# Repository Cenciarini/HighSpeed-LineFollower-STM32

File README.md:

# 🚀 High-Speed Line Follower Robot — STM32 Bluepill

---

## 📖 Descripción general

Este proyecto presenta el desarrollo completo de un **robot móvil seguidor de línea de alta velocidad**, basado en un **microcontrolador STM32F103C8T6 (Bluepill)**.  
El sistema fue diseñado para lograr **gran precisión y estabilidad a altas velocidades** mediante el uso de **controladores PID independientes para cada rueda** y una arquitectura modular que integra hardware, firmware, modelado 3D y una interfaz de control desde PC.

El robot combina múltiples disciplinas de ingeniería:  
- ⚙️ **Diseño electrónico y PCB**  
- 💻 **Programación embebida en C**  
- 🧠 **Control en tiempo real (PID)**  
- 🌐 **Comunicación inalámbrica vía ESP32 / UDP**  
- 🖥️ **Interfaz gráfica en C++ con Qt Creator**  
- 🧩 **Diseño mecánico en SolidWorks**

---

## 🧰 Estructura del repositorio

```
📦 RobotLineFollower_STM32
│
├── PCB_Micro/
│   ├── schematics/
│   ├── gerbers/
│   └── README.md
│   📘 Contiene el diseño electrónico completo en KiCAD.
│
├── QT_Micro/
│   ├── mainwindow.cpp
│   ├── resources/
│   └── README.md
│   💻 Interfaz de usuario en Qt Creator (C++) para control remoto y monitoreo.
│
├── SOLID_Micro/
│   ├── ensamblajes/
│   ├── piezas/
│   └── archivos_stl/
│   🧩 Modelos 3D y partes imprimibles diseñadas en SolidWorks.
│
├── ST_Micro/
│   ├── Core/
│   ├── Drivers/
│   ├── Src/
│   └── Inc/
│   ⚙️ Proyecto en STM32CubeIDE con firmware completo para el Bluepill.
│
└── README.md
```

---

## ⚙️ ST_Micro — Firmware embebido

El firmware principal está implementado en **C** dentro de `STM32CubeIDE`, con soporte para múltiples periféricos del microcontrolador.  
Entre sus módulos más relevantes se incluyen:

### 🔧 Periféricos utilizados
- **I2C:** Lectura de sensor **MPU6050** (acelerómetro + giroscopio).  
- **DMA:** Adquisición continua de señales **ADC** para los sensores IR.  
- **PWM:** Control preciso de la velocidad de cada motor DC.  
- **UART:** Comunicación con módulo **ESP01 (WiFi)** para envío de datos vía UDP.  
- **Timers:** Sincronización de tareas y control de tiempo de muestreo.  
- **ADC:** Lectura analógica de los sensores de línea.  

### 🧠 Control PID
El control PID ajusta dinámicamente las velocidades de ambas ruedas para mantener el robot centrado sobre la línea incluso en curvas pronunciadas o a altas velocidades.

El algoritmo se ejecuta en tiempo real y los parámetros **Kp, Ki, Kd** pueden modificarse desde la interfaz gráfica mediante comunicación **UDP**.

### 🧾 Librerías implementadas
- `comunicaciones.c`: Implementa un protocolo propio con chequeo de errores y estructura de tramas (`HEADER`, `NBYTES`, `PAYLOAD`, `CKS`).  
- `ESP01.c`: Gestión completa del módulo WiFi ESP01 con comandos AT y control de estados.  
- `ssd1306.c` y `fonts.c`: Control del display OLED (visualización de estados del robot).  
- `main.c`: Orquesta la lógica principal, incluyendo adquisición de datos, control PID, comunicación, y visualización en pantalla.

---

## 💻 QT_Micro — Interfaz gráfica de control

Desarrollada en **Qt Creator (C++)**, esta interfaz permite:

- Conexión con el robot a través de **UDP (ESP32 o ESP01)**.  
- Ajuste dinámico de parámetros PID (Kp, Ki, Kd) para cada rueda.  
- Visualización en tiempo real de:
  - Estado del robot y sensores IR.
  - Gráficos del recorrido.
  - Datos del MPU6050 (ángulos, aceleraciones).  
- Control remoto del robot (inicio/parada, velocidad base, direcciones, etc.).

---

## ⚡ PCB_Micro — Electrónica y PCB

Diseñada completamente en **KiCAD**, esta placa integra:

- Microcontrolador **STM32F103C8T6** (Bluepill).  
- Etapa de potencia con control PWM para motores DC.  
- Sensores IR analógicos para detección de línea.  
- Reguladores de tensión y protección de alimentación.  
- Conectores para display OLED, ESP01, MPU6050 y ST-Link.  

Incluye:
- Archivos **.sch** (esquemáticos)
- Archivos **.kicad_pcb**
- Archivos **Gerber** listos para fabricación

---

## 🧩 SOLID_Micro — Diseño mecánico

El diseño mecánico del robot fue modelado íntegramente en **SolidWorks**, con foco en minimizar peso y tamaño manteniendo la rigidez estructural.  
Se incluyen:
- Ensambles del chasis y soporte de sensores.  
- Piezas STL listas para impresión 3D.  
- Montaje optimizado del PCB y baterías.

---

## 📡 Comunicación y protocolo

El robot y la interfaz de PC se comunican mediante **UDP**, usando un **protocolo propio de mensajes binarios** desarrollado en C.  
Cada mensaje posee estructura de seguridad y verificación de checksum, garantizando robustez en entornos de alta velocidad.

---

## 🧠 Principales características técnicas

| Componente | Descripción |
|-------------|-------------|
| **Microcontrolador** | STM32F103C8T6 (Cortex-M3, 72 MHz) |
| **Sensores** | IR analógicos + MPU6050 (I2C) |
| **Pantalla** | OLED SSD1306 (I2C) |
| **Comunicación** | ESP01 (UART → UDP) / Interfaz Qt |
| **Control** | PID doble canal (rueda izquierda / derecha) |
| **Alimentación** | Batería Li-Po 7.4V con regulación interna |
| **Software principal** | STM32CubeIDE, KiCAD, Qt Creator, SolidWorks |

---

## 🧠 Habilidades demostradas

Este proyecto refleja competencias avanzadas en:

- Diseño y fabricación de **PCBs profesionales** con KiCAD.  
- Programación de **firmware embebido en C para microcontroladores STM32**.  
- Implementación de **controladores PID en tiempo real**.  
- Desarrollo de **protocolos de comunicación personalizados**.  
- Integración de **periféricos complejos (ADC, DMA, I2C, UART, PWM)**.  
- Diseño de **interfaces gráficas multiplataforma (Qt Creator)**.  
- Diseño **mecánico 3D y prototipado rápido (SolidWorks)**.  

---

## 📄 Licencia

Este proyecto está licenciado bajo los términos de la **MIT License**.  
Consulta el archivo [LICENSE](LICENSE) para más información.

---

## 👤 Autor

**Gabriel Cenciarini**  
Ingeniero Mecatrónico
📧 [LinkedIn](https://www.linkedin.com/in/cenciarinigabriel/) | 💻 [GitHub](https://github.com/Cenciarini)

---

> “La integración entre electrónica, software y control no solo construye robots, sino ingenieros capaces de pensar en sistemas completos.”

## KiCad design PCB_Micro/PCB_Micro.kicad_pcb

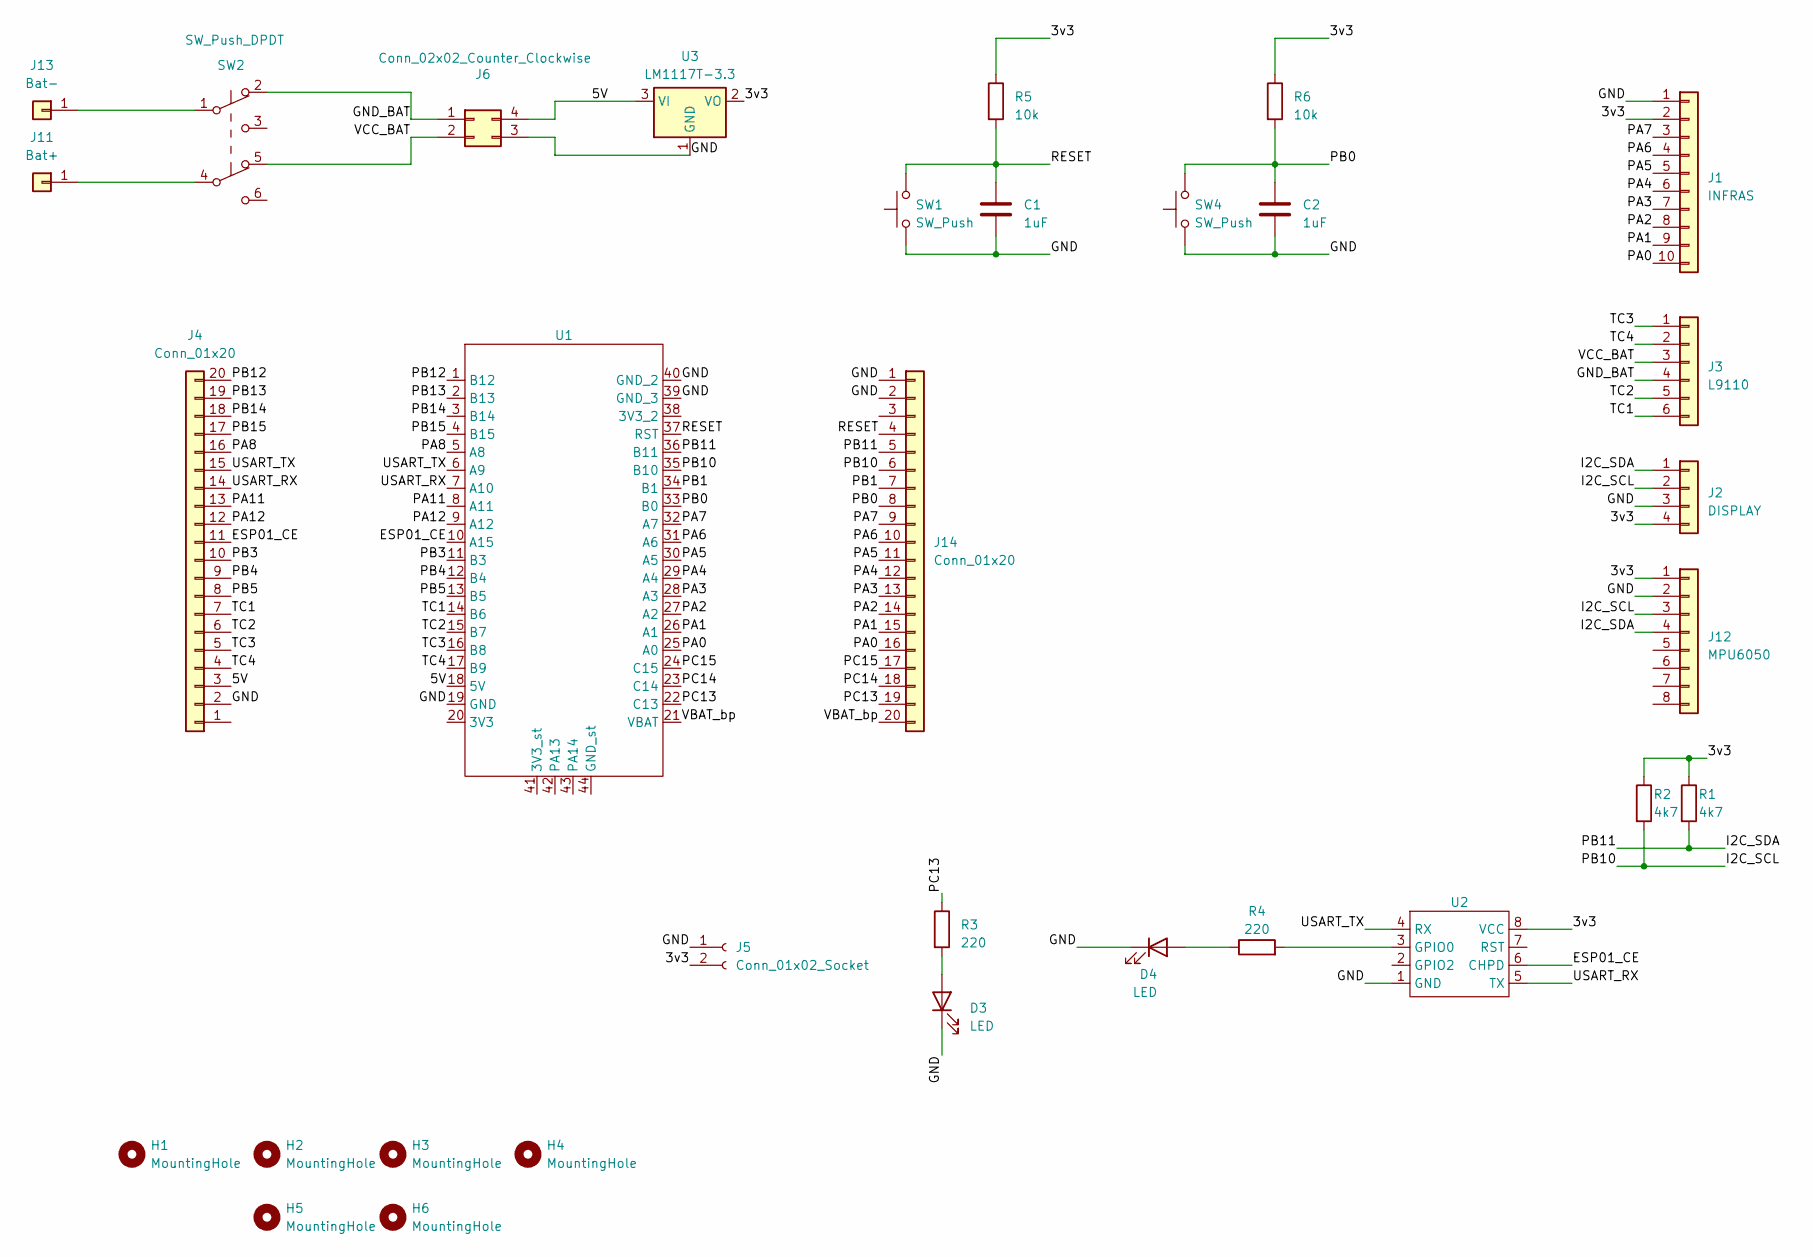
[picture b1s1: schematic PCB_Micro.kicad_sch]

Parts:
C1, C2: 1uF; C_Disc_D3.8mm_W2.6mm_P2.50mm
D3, D4: LED; LED_D3.0mm
H1, H2, H3, H4, H5, H6: MountingHole; MountingHole_3.2mm_M3
J1: INFRAS; PinHeader_1x10_P2.54mm_Horizontal
J2: DISPLAY; PinSocket_1x04_P2.54mm_Vertical
J3: L9110; PinSocket_1x06_P2.54mm_Vertical
J4, J14: Conn_01x20; PinSocket_1x20_P2.54mm_Vertical
J5: Conn_01x02_Socket; PinSocket_1x02_P2.54mm_Vertical
J6: Conn_02x02_Counter_Clockwise; MINI360Module
J11: Bat+; PinSocket_1x01_P2.54mm_Vertical
J12: MPU6050; PinSocket_1x08_P2.54mm_Vertical
J13: Bat-; PinSocket_1x01_P2.54mm_Vertical
R1, R2: 4k7; R_Axial_DIN0207_L6.3mm_D2.5mm_P10.16mm_Horizontal
R3, R4: 220; R_Axial_DIN0207_L6.3mm_D2.5mm_P10.16mm_Horizontal
R5, R6: 10k; R_Axial_DIN0207_L6.3mm_D2.5mm_P10.16mm_Horizontal
SW1, SW4: SW_Push; SW_PUSH_6mm_H4.3mm
SW2: SW_Push_DPDT; SW_Push_2P2T_Toggle_CK_PVA2xxH1xxxxxxV2
U1: STM32BluePill
U2: XCVR_ESP8266-01_ESP-01
U3: LM1117T-3.3; TO-220-3_Vertical

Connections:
/3v3: J1.2, J2.4, J5.2, J12.1, R1.1, R2.1, R5.1, R6.1, U2.8 (VCC), U3.2 (VO)
/5V: J4.3, J6.4, U1.18 (5V), U3.3 (VI)
/ESP01_CE: J4.11, U1.10 (A15), U2.6 (CHPD)
/GND: C1.2, C2.2, D3.1 (K), D4.1 (K), J1.1, J2.3, J4.2, J5.1, J6.3, J12.2, J14.1, J14.2, SW1.1, SW4.1, U1.19 (GND), U1.39 (GND_3), U1.40 (GND_2), U2.1 (GND), U3.1 (GND)
/GND_BAT: J3.4, J6.1, SW2.2 (A)
/I2C_SCL: J2.2, J12.3, J14.6, R2.2, U1.35 (B10)
/I2C_SDA: J2.1, J12.4, J14.5, R1.2, U1.36 (B11)
/PA0: J1.10, J14.16, U1.25 (A0)
/PA1: J1.9, J14.15, U1.26 (A1)
/PA2: J1.8, J14.14, U1.27 (A2)
/PA3: J1.7, J14.13, U1.28 (A3)
/PA4: J1.6, J14.12, U1.29 (A4)
/PA5: J1.5, J14.11, U1.30 (A5)
/PA6: J1.4, J14.10, U1.31 (A6)
/PA7: J1.3, J14.9, U1.32 (A7)
/PA8: J4.16, U1.5 (A8)
/PA11: J4.13, U1.8 (A11)
/PA12: J4.12, U1.9 (A12)
/PB0: C2.1, J14.8, R6.2, SW4.2, U1.33 (B0)
/PB1: J14.7, U1.34 (B1)
/PB3: J4.10, U1.11 (B3)
/PB4: J4.9, U1.12 (B4)
/PB5: J4.8, U1.13 (B5)
/PB12: J4.20, U1.1 (B12)
/PB13: J4.19, U1.2 (B13)
/PB14: J4.18, U1.3 (B14)
/PB15: J4.17, U1.4 (B15)
/PC13: J14.19, R3.1, U1.22 (C13)
/PC14: J14.18, U1.23 (C14)
/PC15: J14.17, U1.24 (C15)
/RESET: C1.1, J14.4, R5.2, SW1.2, U1.37 (RST)
/TC1: J3.6, J4.7, U1.14 (B6)
/TC2: J3.5, J4.6, U1.15 (B7)
/TC3: J3.1, J4.5, U1.16 (B8)
/TC4: J3.2, J4.4, U1.17 (B9)
/USART_RX: J4.14, U1.7 (A10), U2.5 (TX)
/USART_TX: J4.15, U1.6 (A9), U2.4 (RX)
/VBAT_bp: J14.20, U1.21 (VBAT)
/VCC_BAT: J3.3, J6.2, SW2.5 (A)
unnamed: D3.2 (A), R3.2
unnamed: D4.2 (A), R4.1
unnamed: J11.1, SW2.4 (B)
unnamed: J13.1, SW2.1 (B)
unnamed: R4.2, U2.3 (GPIO0)

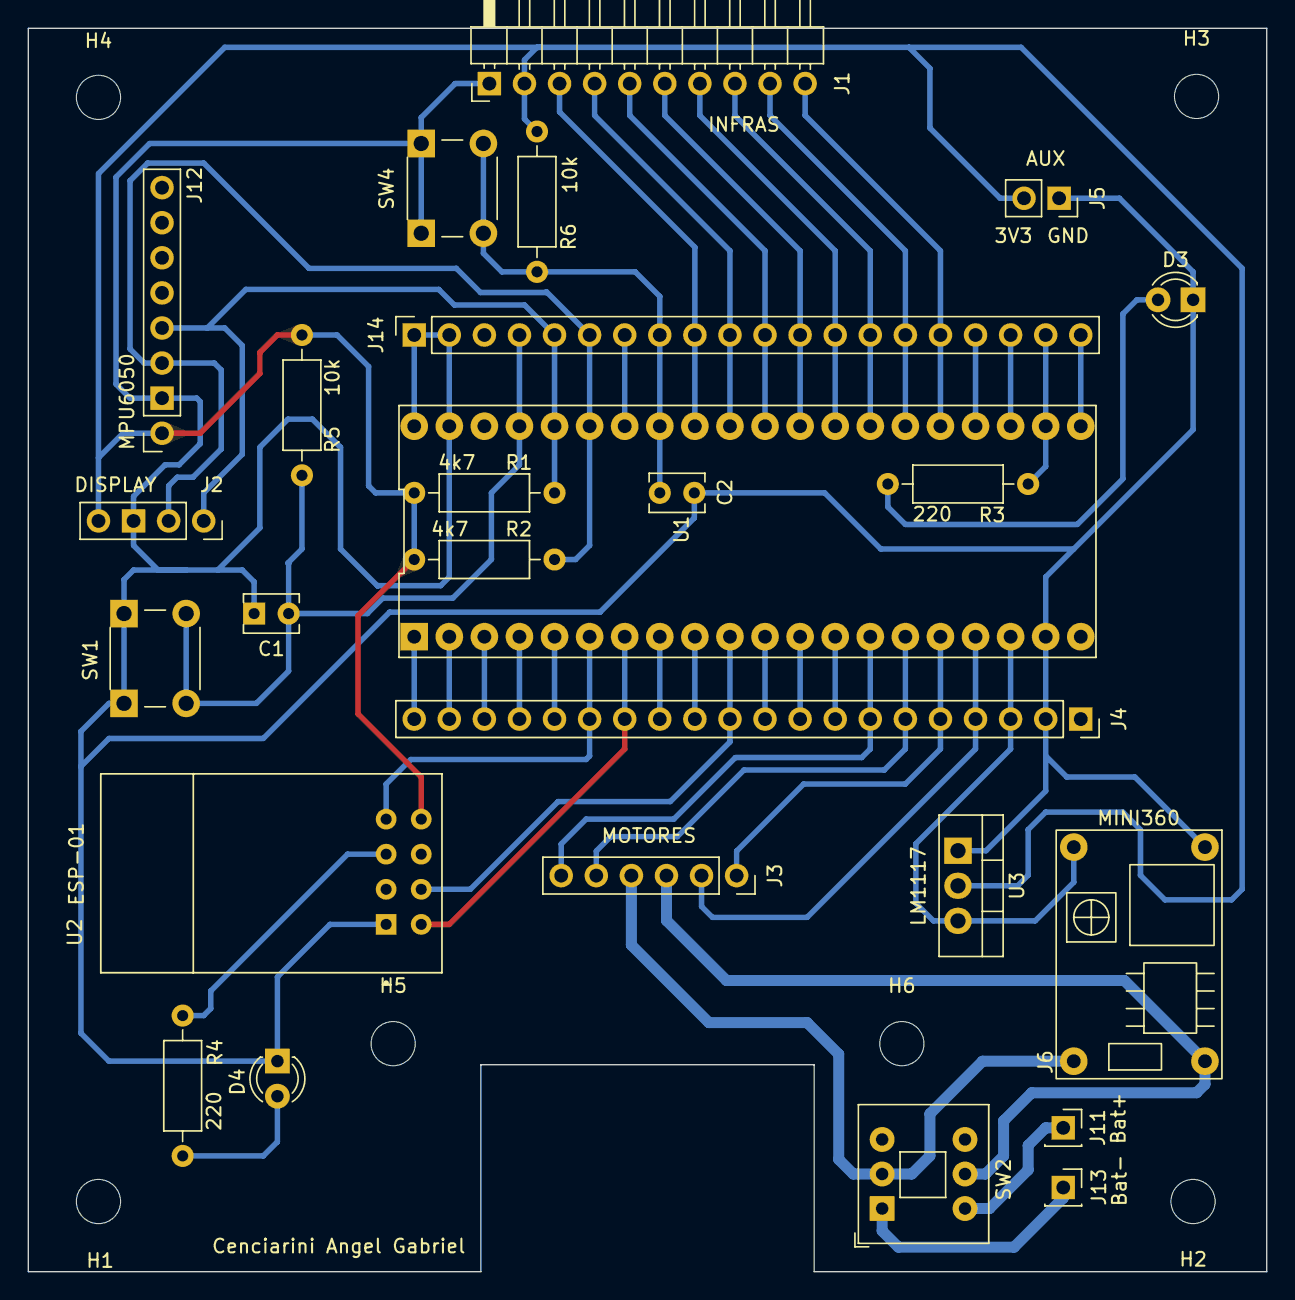
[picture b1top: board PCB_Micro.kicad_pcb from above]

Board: 2 copper layers, 89.7 x 90.0 mm, 32 parts (0 on the bottom side), 44 nets.

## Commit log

2025-10-17 Versión inicial del robot seguidor de línea con STM32 Bluepill
2025-10-17 add README via upload

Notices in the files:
README.md:
License: MIT
